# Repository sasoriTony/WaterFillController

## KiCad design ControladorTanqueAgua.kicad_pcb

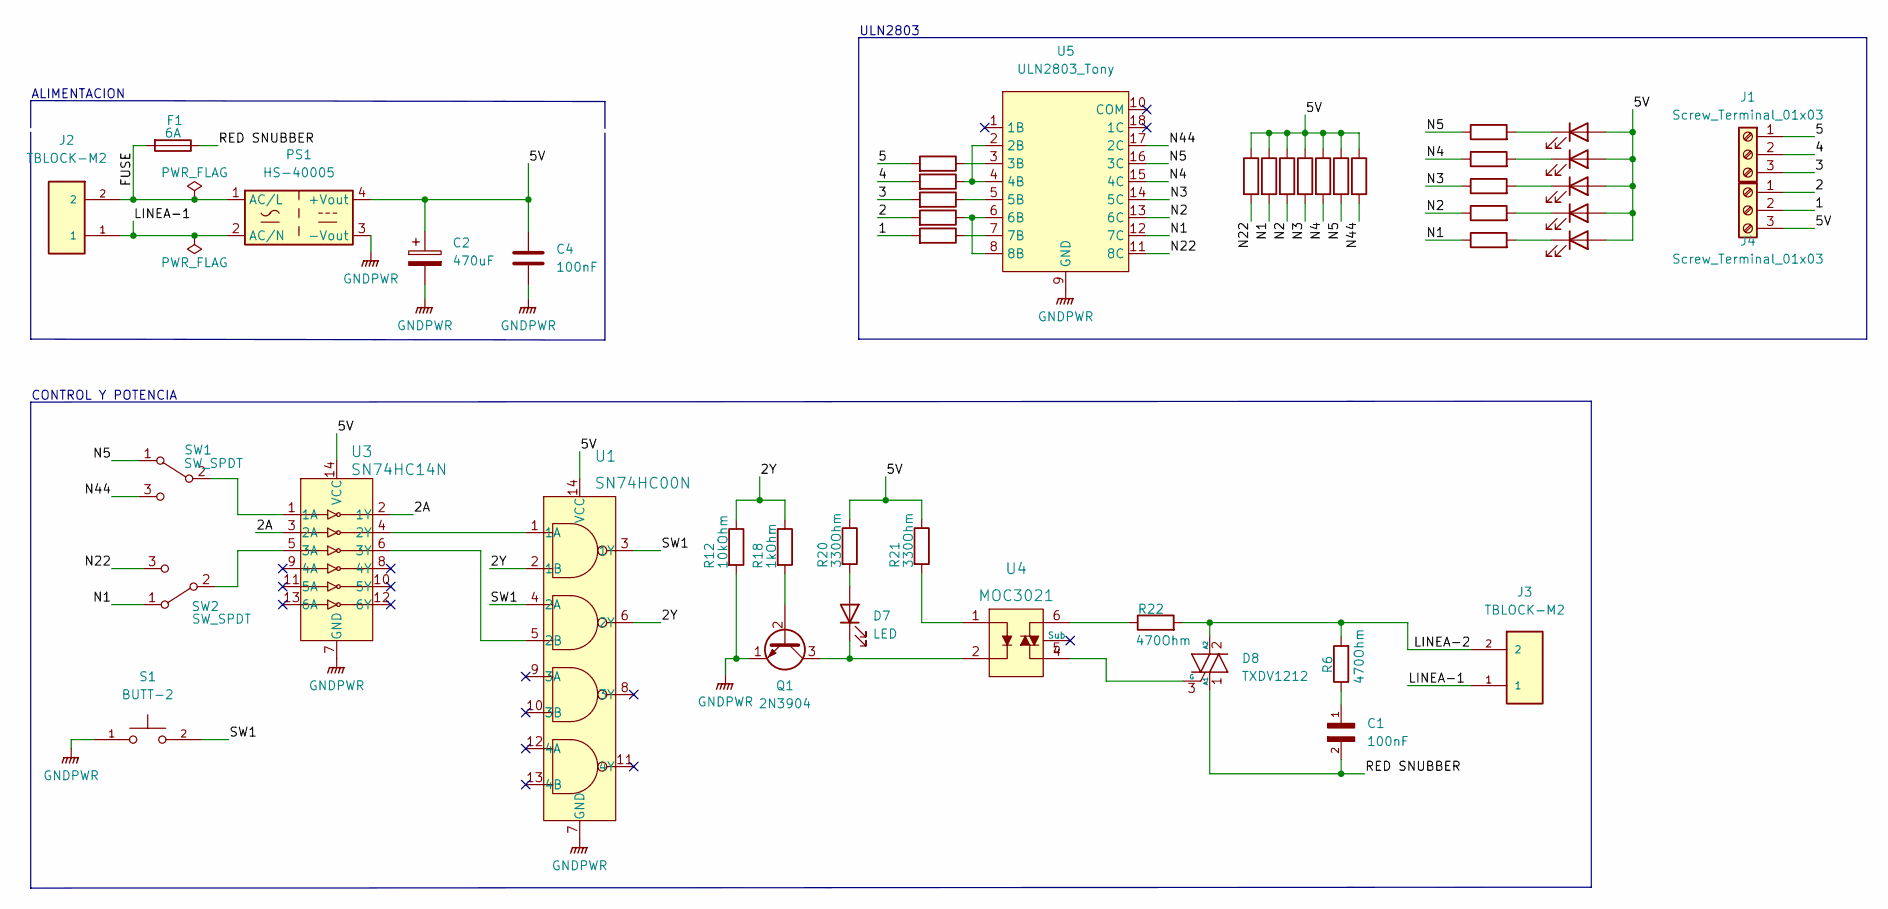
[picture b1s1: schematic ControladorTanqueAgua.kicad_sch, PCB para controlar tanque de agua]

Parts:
C1: 100nF; MetallizedPolypropyleneFilmCapacitor; PARTREV 31-Jul-19
C2: 470uF; CP_Radial_D10.0mm_P5.00mm
C4: 100nF; C_Disc_D5.0mm_W2.5mm_P5.00mm
D1, D3, D4, D5, D6, D7: LED; LED_D5.0mm
D8: TXDV1212; TO-220-3_L10.0-W4.5-P2.54-L_TRIAC
F1: 6A; FUSE-TH_L22.6-W9.0
J1, J4: Screw_Terminal_01x03; TerminalBlock_Phoenix_MKDS-1,5-3_1x03_P5.00mm_Horizontal
J2, J3: TBLOCK-M2; CONN-TH_2P-P9.50_DBT50G-9.5-2P_BORNERA_220VAC_Sasori
PS1: HS-40005; PWRM-TH_TAS5-X-WEDT-CONVERTER-AC-DC_Sasori
Q1: 2N3904; TO-92_Inline_Wide
R1, R2, R3, R4, R5, R13, R14, R15, R16, R17, R20, R21: 330Ohm; RES-TH_BD2.2-L6.5-P10.50-D0.9_Carbon
R6, R22: 470Ohm; RES-TH_BD2.2-L6.5-P10.50-D0.9_Carbon
R7, R8, R9, R10, R11, R12, R19, R23: 10kOhm; RES-TH_BD2.2-L6.5-P10.50-D0.9_Carbon
R18: 1kOhm; RES-TH_BD2.2-L6.5-P10.50-D0.9_Carbon
S1: BUTT-2; SW_BUTT-2; PARTREV N/A
SW1, SW2: SW_SPDT; SW-TH_DEALON_SS-12D01-GX
U1: SN74HC00N; DIP-14_L19.0-W7.0-P2.54-LS7.6-BL; MPN SN74HC00N; Digi-Key_PN 296-1563-5-ND
U3: SN74HC14N; DIP-14_L19.1-W6.4-P2.54-LS7.6-BL; MPN SN74HC14N; Digi-Key_PN 296-1577-5-ND
U4: MOC3021; DIP-6_L8.5-W6.4-P2.54-LS7.6-BL_MOC3021; MPN MOC3021; Digi-Key_PN 160-1374-5-ND
U5: ULN2803_Tony; DIP-18_L23.0-W6.5-P2.54-LS7.6-BL

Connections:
/1: J4.2, R5.2
/2: J4.1, R4.2
/2A: U3.2 (1Y), U3.3 (2A)
/2Y: R12.1, R18.1, U1.2 (1B), U1.6 (2Y)
/3: J1.3, R3.2
/4: J1.2, R1.2
/5: J1.1, R2.2
/5V: C2.1, C4.1, D1.2 (A), D3.2 (A), D4.2 (A), D5.2 (A), D6.2 (A), J4.3, PS1.4 (+Vout), R7.1, R8.1, R9.1, R10.1, R11.1, R19.1, R20.1, R21.1, R23.1, U1.14 (VCC), U3.14 (VCC)
/FUSE: F1.2, J2.2, PS1.1 (AC/L)
/LINEA-1: J2.1, J3.1, PS1.2 (AC/N)
/LINEA-2: D8.2 (A2), J3.2, R6.2, R22.2
/N1: R7.2, R13.1, SW2.1 (A), U5.12 (7C)
/N2: R8.2, R14.1, U5.13 (6C)
/N3: R9.2, R15.1, U5.14 (5C)
/N4: R10.2, R16.1, U5.15 (4C)
/N5: R11.2, R17.1, SW1.1 (A), U5.16 (3C)
/N22: R19.2, SW2.3 (C), U5.11 (8C)
/N44: R23.2, SW1.3 (C), U5.17 (2C)
/RED SNUBBER: C1.2, D8.1 (A1), F1.1
/SW1: S1.2, U1.3 (1Y), U1.4 (2A)
GNDPWR: C2.2, C4.2, PS1.3 (-Vout), Q1.1 (E), R12.2, S1.1, U1.7 (GND), U3.7 (GND), U5.9 (GND)
unnamed: C1.1, R6.1
unnamed: D1.1 (K), R13.2
unnamed: D3.1 (K), R14.2
unnamed: D4.1 (K), R16.2
unnamed: D5.1 (K), R15.2
unnamed: D6.1 (K), R17.2
unnamed: D7.1 (K), Q1.3 (C), U4.2
unnamed: D7.2 (A), R20.2
unnamed: D8.3 (G), U4.4
unnamed: Q1.2 (B), R18.2
unnamed: R1.1, U5.2 (2B), U5.4 (4B)
unnamed: R2.1, U5.3 (3B)
unnamed: R3.1, U5.5 (5B)
unnamed: R4.1, U5.6 (6B), U5.8 (8B)
unnamed: R5.1, U5.7 (7B)
unnamed: R21.2, U4.1
unnamed: R22.1, U4.6
unnamed: SW1.2 (B), U3.1 (1A)
unnamed: SW2.2 (B), U3.5 (3A)
unnamed: U1.1 (1A), U3.4 (2Y)
unnamed: U1.5 (2B), U3.6 (3Y)

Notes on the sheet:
ALIMENTACION
CONTROL Y POTENCIA
ULN2803

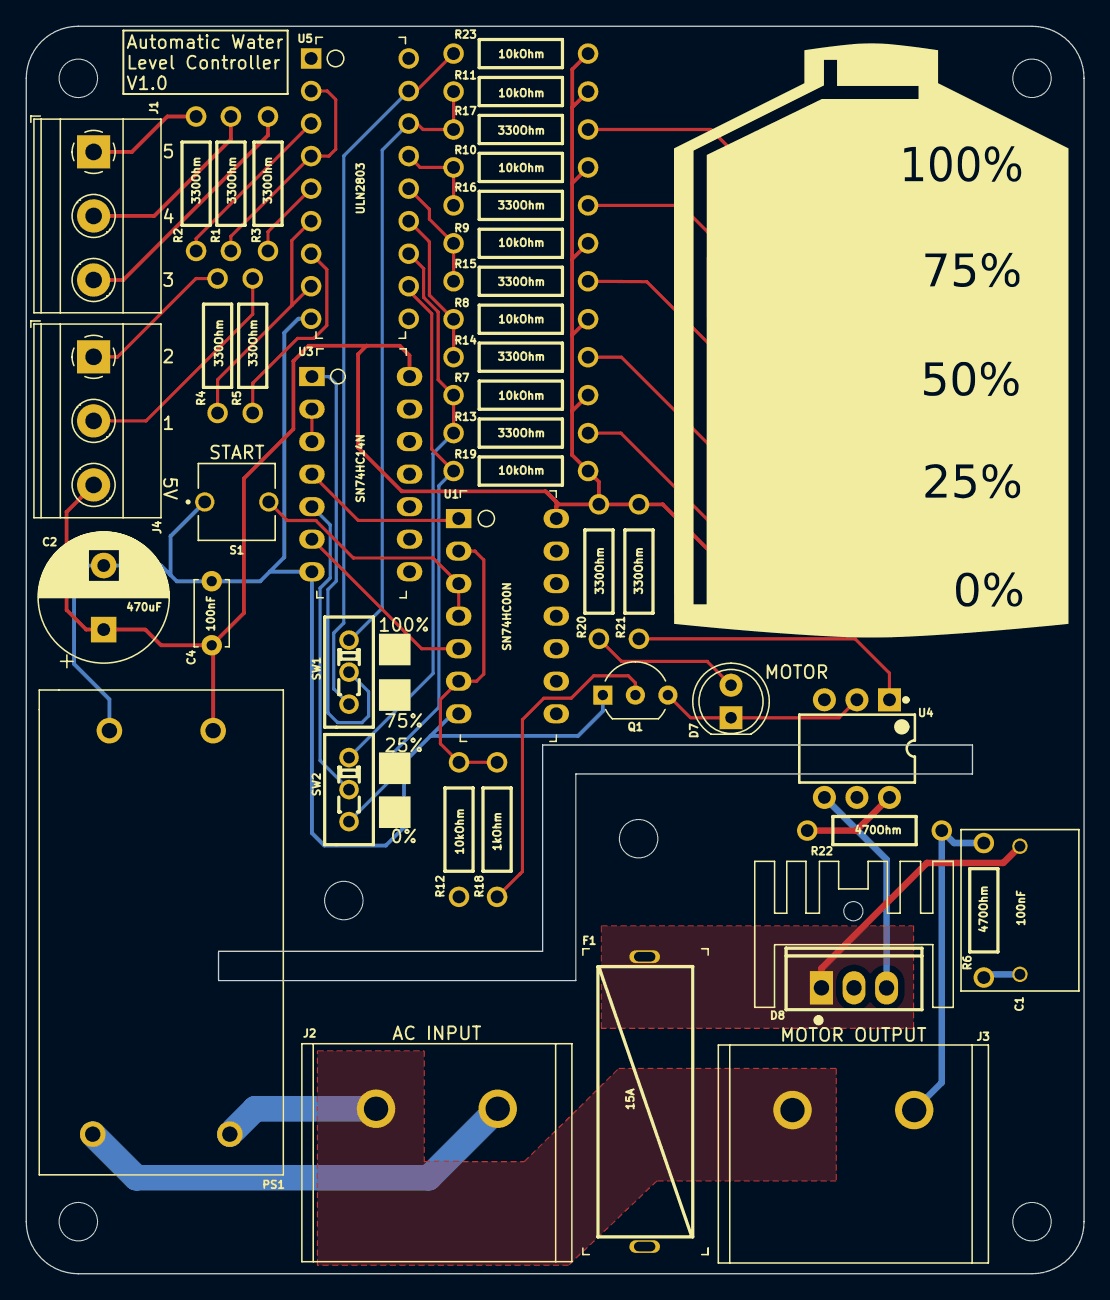
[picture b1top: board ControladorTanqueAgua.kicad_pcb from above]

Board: 2 copper layers, 82.6 x 97.4 mm, 51 parts (0 on the bottom side), 42 nets.

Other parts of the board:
0%, 25%, 75%, 100%: LOGO; cuadrado_inkscape

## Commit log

2022-11-05 First commit.
2022-11-05 Added a Board Characteristics.
2022-11-05 Moved Board Characteristics.
2022-11-06 Moved Board Characteristics 2.
